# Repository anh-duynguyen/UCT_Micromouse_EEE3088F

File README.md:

# UCT Micromouse EEE3088F Project

## Description
This project is for the development and design of Sensing and Power Modules for a micromouse in EEE3088F 2024. This repo is further used for the development of the UCT Micromouse in the 2nd semester Third Year Design Course, EEE3097S, EEE3098S and EEE3099S. 

## Structure
- **PCB**: 
  - The KiCAD Project
  - Schematics & Layout
  - Project Footprints

- **Software**: 
  - Any software developed for the hardware
  - Instructions on where to find relevant software

- **Documents**: 
  - Project documentation
  - Component datasheets

## Usage
The project documentation can be found in the Documents directory and the files required to produce the PCB can be found in the Production directory.

## Contact
- Anh Duy Nguyen
- Ronald Walters

## Project Status and Roadmap
This project is actively under developement.

## Authors and Acknowledgement
### Authors:
- Anh Duy Nguyen
- Ronald Walters

## License
GPL-2.0 license

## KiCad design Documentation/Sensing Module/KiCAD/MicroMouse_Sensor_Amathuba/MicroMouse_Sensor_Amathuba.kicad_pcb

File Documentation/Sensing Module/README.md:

# Sensing Module

This section contains datasheets and informational documents related to the sensors used and considered, as well as information about the STM32.

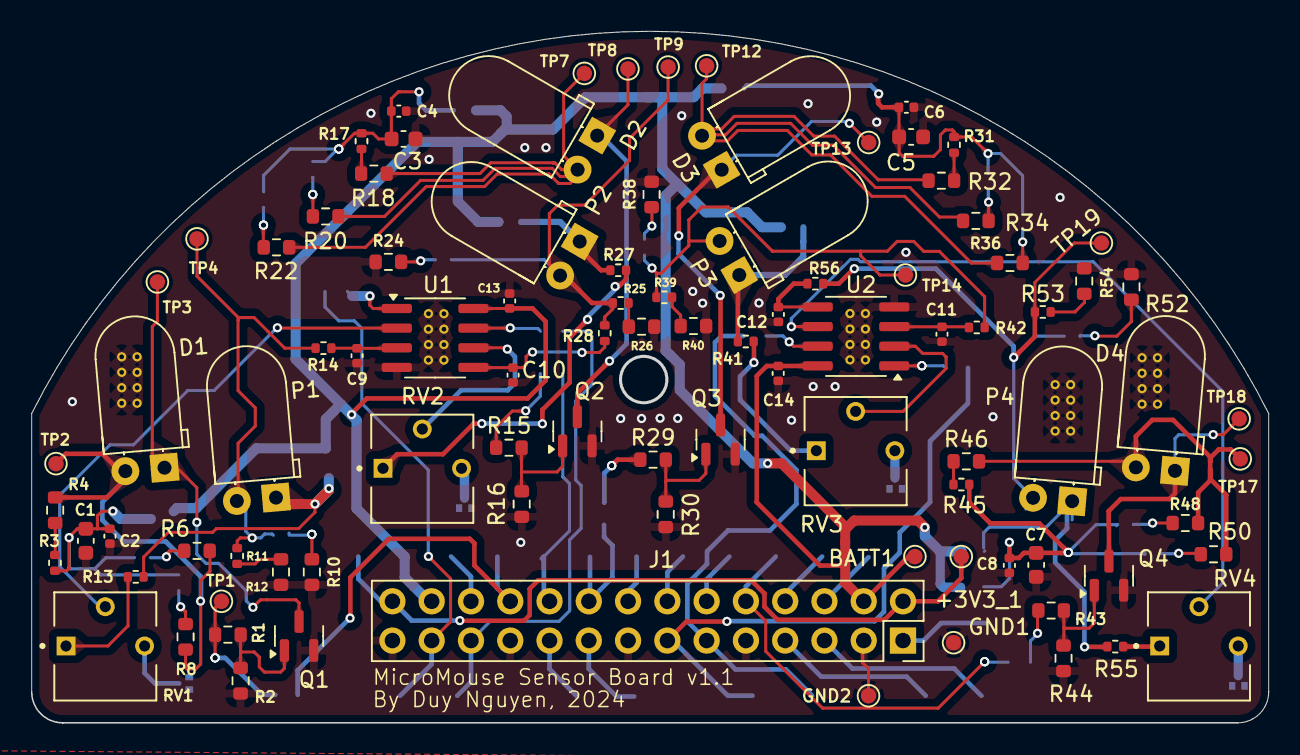
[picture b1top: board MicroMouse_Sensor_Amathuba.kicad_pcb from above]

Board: 2 copper layers, 79.9 x 44.6 mm, 150 parts (0 on the bottom side), 90 nets.

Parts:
+3V3_1, +3V3_2: TestPoint; TestPoint_Pad_D1.0mm
AB0: TestPoint; TestPoint_Pad_D1.0mm
BATT1, BATT2: TestPoint; TestPoint_Pad_D1.0mm
C1, C3, C5, C7: 4.7µF; C_0603_1608Metric
C2, C4, C6, C8, C9, C10, C11, C12: 100nF; C_0402_1005Metric
C13, C14: 1uF; C_0402_1005Metric
D1, D2, D3, D4: SFH 4544; LED_D5.0mm_Horizontal_O1.27mm_Z3.0mm_IRGrey
GND1, GND2, GND3, GND4, GND5: TestPoint; TestPoint_Pad_D1.0mm
J1: Conn_02x14_Odd_Even; PinSocket_2x14_P2.54mm_Vertical
JP1, JP2, JP4, JP5, JP6, JP7, JP9, JP10, JP11, JP12, JP14, JP15, JP16, JP17, JP19, JP20: SolderJumper_2_Open; SolderJumper-2_P1.3mm_Open_TrianglePad1.0x1.5mm
JP3, JP8, JP13, JP18: SolderJumper_2_Bridged; SolderJumper-2_P1.3mm_Bridged2Bar_RoundedPad1.0x1.5mm
P1, P2, P3, P4: PD333-3B/H0/L2; LED_D5.0mm_Horizontal_O1.27mm_Z3.0mm
PA3, PA4, PA5, PA6, PA7: TestPoint; TestPoint_Pad_D1.0mm
PC4, PC5: TestPoint; TestPoint_Pad_D1.0mm
PE8, PE9, PE10, PE11, PE12, PE13, PE14, PE15: TestPoint; TestPoint_Pad_D1.0mm
Q1, Q2, Q3, Q4: 2N7002; SOT-23
R1, R6, R15, R20, R29, R34, R43, R48: 100Ω; R_0603_1608Metric
R2, R16, R30, R44: 47kΩ; R_0603_1608Metric
R3, R5, R7, R9, R11, R13, R14, R17, R19, R21, R23, R25, R27, R28, R31, R33, R35, R37, R39, R41, R42, R45, R47, R49, R51, R53, R55, R56: 0Ω; R_0402_1005Metric
R4, R18, R32, R46: 51Ω; R_0603_1608Metric
R8, R22, R36, R50: 20Ω; R_0603_1608Metric
R10, R24, R38, R52: 100kΩ; R_0603_1608Metric
R12, R26, R40, R54: 10kΩ; R_0603_1608Metric
RESV1, RESV2, RESV3: TestPoint; TestPoint_Pad_D1.0mm
RV1, RV2, RV3, RV4: 10k; TRIM_3362P-1-103
TP1, TP2, TP3, TP4, TP7, TP8, TP9, TP12, TP13, TP14, TP17, TP18, TP19: TestPoint; TestPoint_Pad_D1.0mm
U1, U2: MCP6002T-I/SN; SOIC-8_3.9x4.9mm_P1.27mm

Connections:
+3V3: +3V3_1.1, +3V3_2.1, J1.2, J1.28
+BATT: BATT1.1, BATT2.1, C13.1, C14.1, J1.4, J1.26, JP2.1 (A), JP4.1 (A), JP7.1 (A), JP9.1 (A), JP12.1 (A), JP14.1 (A), JP17.1 (A), JP19.1 (A), U1.8 (V+), U2.8 (V+)
/AB0: AB0.1, J1.25, JP5.1 (A)
/PA3: J1.5, PA3.1
/PA4: J1.7, PA4.1
/PA5: J1.11, JP20.1 (A), PA5.1
/PA6: J1.13, JP15.1 (A), PA6.1
/PA7: J1.17, PA7.1
/PC4: J1.19, PC4.1
/PC5: J1.23, JP10.1 (A), PC5.1
/PE8: J1.22, JP1.1 (A), PE8.1
/PE9: J1.20, JP6.1 (A), PE9.1
/PE10: J1.18, JP11.1 (A), PE10.1
/PE11: J1.16, PE11.1
/PE12: J1.14, PE12.1
/PE13: J1.12, PE13.1
/PE14: J1.10, JP16.1 (A), PE14.1
/PE15: J1.8, PE15.1
/RESV1: J1.24, RESV1.1
/RESV2: J1.6, RESV2.1
/RESV3: J1.1, RESV3.1
GND: C1.2, C2.2, C3.2, C4.2, C5.2, C6.2, C7.2, C8.2, C9.2, C10.2, C11.2, C12.2, C13.2, C14.2, GND1.1, GND2.1, GND3.1, GND4.1, GND5.1, J1.3, J1.9, J1.15, J1.21, J1.27, JP3.1 (A), JP8.1 (A), JP13.1 (A), JP18.1 (A), Q1.2 (S), Q2.2 (S), Q3.2 (S), Q4.2 (S), R2.2, R10.2, R12.2, R16.2, R24.2, R26.2, R30.2, R38.2, R40.2, R44.2, R52.2, R54.2, U1.4 (V-), U2.4 (V-)
unnamed: D1.2 (A), R4.2, R6.2, R8.2, TP2.1
unnamed: D1.1 (K), Q1.3 (D), TP3.1
unnamed: D2.2 (A), R18.2, R20.2, R22.2, TP7.1
unnamed: D2.1 (K), Q2.3 (D), TP8.1
unnamed: D3.2 (A), R32.2, R34.2, R36.2, TP12.1
unnamed: D3.1 (K), Q3.3 (D), TP13.1
unnamed: D4.2 (A), R46.2, R48.2, R50.2, TP17.1
unnamed: D4.1 (K), Q4.3 (D), TP18.1
unnamed: JP1.2 (B), R1.1, TP1.1
unnamed: C1.1, C2.1, JP2.2 (B), R3.1, R5.1, R7.1
unnamed: JP3.2 (B), RV1.3
unnamed: JP4.2 (B), P1.1 (K), R13.1
unnamed: JP5.2 (B), U1.1
unnamed: JP6.2 (B), R15.1
unnamed: C3.1, C4.1, JP7.2 (B), R17.1, R19.1, R21.1
unnamed: JP8.2 (B), RV2.3
unnamed: JP9.2 (B), P2.1 (K), R27.1
unnamed: JP10.2 (B), U1.7
unnamed: JP11.2 (B), R29.1
unnamed: C5.1, C6.1, JP12.2 (B), R31.1, R33.1, R35.1
unnamed: JP13.2 (B), RV3.3
unnamed: JP14.2 (B), P3.1 (K), R41.1
unnamed: JP15.2 (B), U2.1
unnamed: JP16.2 (B), R43.1
unnamed: C7.1, C8.1, JP17.2 (B), R45.1, R47.1, R49.1
unnamed: JP18.2 (B), RV4.3
unnamed: JP19.2 (B), P4.1 (K), R55.1
unnamed: JP20.2 (B), U2.7
unnamed: P1.2 (A), R9.1, R11.1, R14.1, TP4.1
unnamed: P2.2 (A), R23.1, R25.1, R28.1, TP9.1
unnamed: P3.2 (A), R37.1, R39.1, R42.1, TP14.1
unnamed: P4.2 (A), R51.1, R53.1, R56.1, TP19.1
unnamed: Q1.1 (G), R1.2, R2.1
unnamed: Q2.1 (G), R15.2, R16.1
unnamed: Q3.1 (G), R29.2, R30.1
unnamed: Q4.1 (G), R43.2, R44.1
unnamed: R3.2, R4.1
unnamed: R5.2, R6.1
unnamed: R7.2, R8.1
unnamed: R9.2, R10.1
unnamed: R11.2, R12.1
unnamed: R13.2, RV1.1
unnamed: R17.2, R18.1
unnamed: R19.2, R20.1
unnamed: R21.2, R22.1
unnamed: R23.2, R24.1
unnamed: R25.2, R26.1
unnamed: R27.2, RV2.1
unnamed: R31.2, R32.1
unnamed: R33.2, R34.1
unnamed: R35.2, R36.1
unnamed: R37.2, R38.1
unnamed: R39.2, R40.1
unnamed: R41.2, RV3.1
unnamed: R45.2, R46.1
unnamed: R47.2, R48.1
unnamed: R49.2, R50.1
unnamed: R51.2, R52.1
unnamed: R53.2, R54.1
unnamed: R55.2, RV4.1
unnamed: C9.1, R14.2, U1.3 (+)
unnamed: RV1.2, U1.2 (-)
unnamed: C10.1, R28.2, U1.5 (+)
unnamed: RV2.2, U1.6 (-)
unnamed: C11.1, R42.2, U2.3 (+)
unnamed: RV3.2, U2.2 (-)
unnamed: C12.1, R56.2, U2.5 (+)
unnamed: RV4.2, U2.6 (-)

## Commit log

2024-03-14 Create README.md
    Creating README.md
2024-03-18 Create LICENSE
2024-03-18 Create Component Datasheets
2024-03-18 Project Files
2024-03-18 Create README.md for Power
2024-03-18 Create README.md for Reports
2024-03-18 Breadboard Brief
2024-03-18 STM32 Datasheet
2024-03-18 Create README.md for Power Datasheets
2024-03-18 STM32 Datasheet for Power
2024-03-18 Create README.md for formatting
2024-03-18 Update README.md for Repo
2024-03-18 LICENSE
2024-03-18 TSAL6400
2024-03-18 Create README.md for Footprints
2024-03-18 Adding footprints
2024-03-28 Added Latex Report Template
2024-04-07 Power Subsystem Active Component Datasheets
2024-04-07 Power Subsystem Active Component Footprints
2024-04-09 Create gitignore
2024-04-21 Create KiCAD
2024-04-21 Kicad
2024-04-21 Uploaded Interim Report
2024-04-21 Incomplete Report Submitted...
    The constraint of limited knowledge required to write a report, well-formatted, with tables and figures, was a limitation I did not foresee in advance. This led to unforeseen delays in compiling the 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
2024-04-21 Schematic Quality Improvement Technique
    By;
    i) Printing the KiCad schematic (CTRL+P)
    ii) Then selecting to save a .PDF copy
    iii) One can open the .pdf in Adobe Illustrator
    iv) crop the image by selecting the rectangle tool on the side bar
    v) and cover the desired image with the blank rectangle
2024-05-06 Schematic Quality Improvement Technique Correction
2024-05-17 Code Uploaded. Large File
2024-07-29 Create EEE3089-99S
2024-07-29 current progress on status report
